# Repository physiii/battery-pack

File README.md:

# battery-pack
60v battery pack using 16 (18650) batteries with voltage level LED.

##Schematic

##Layout

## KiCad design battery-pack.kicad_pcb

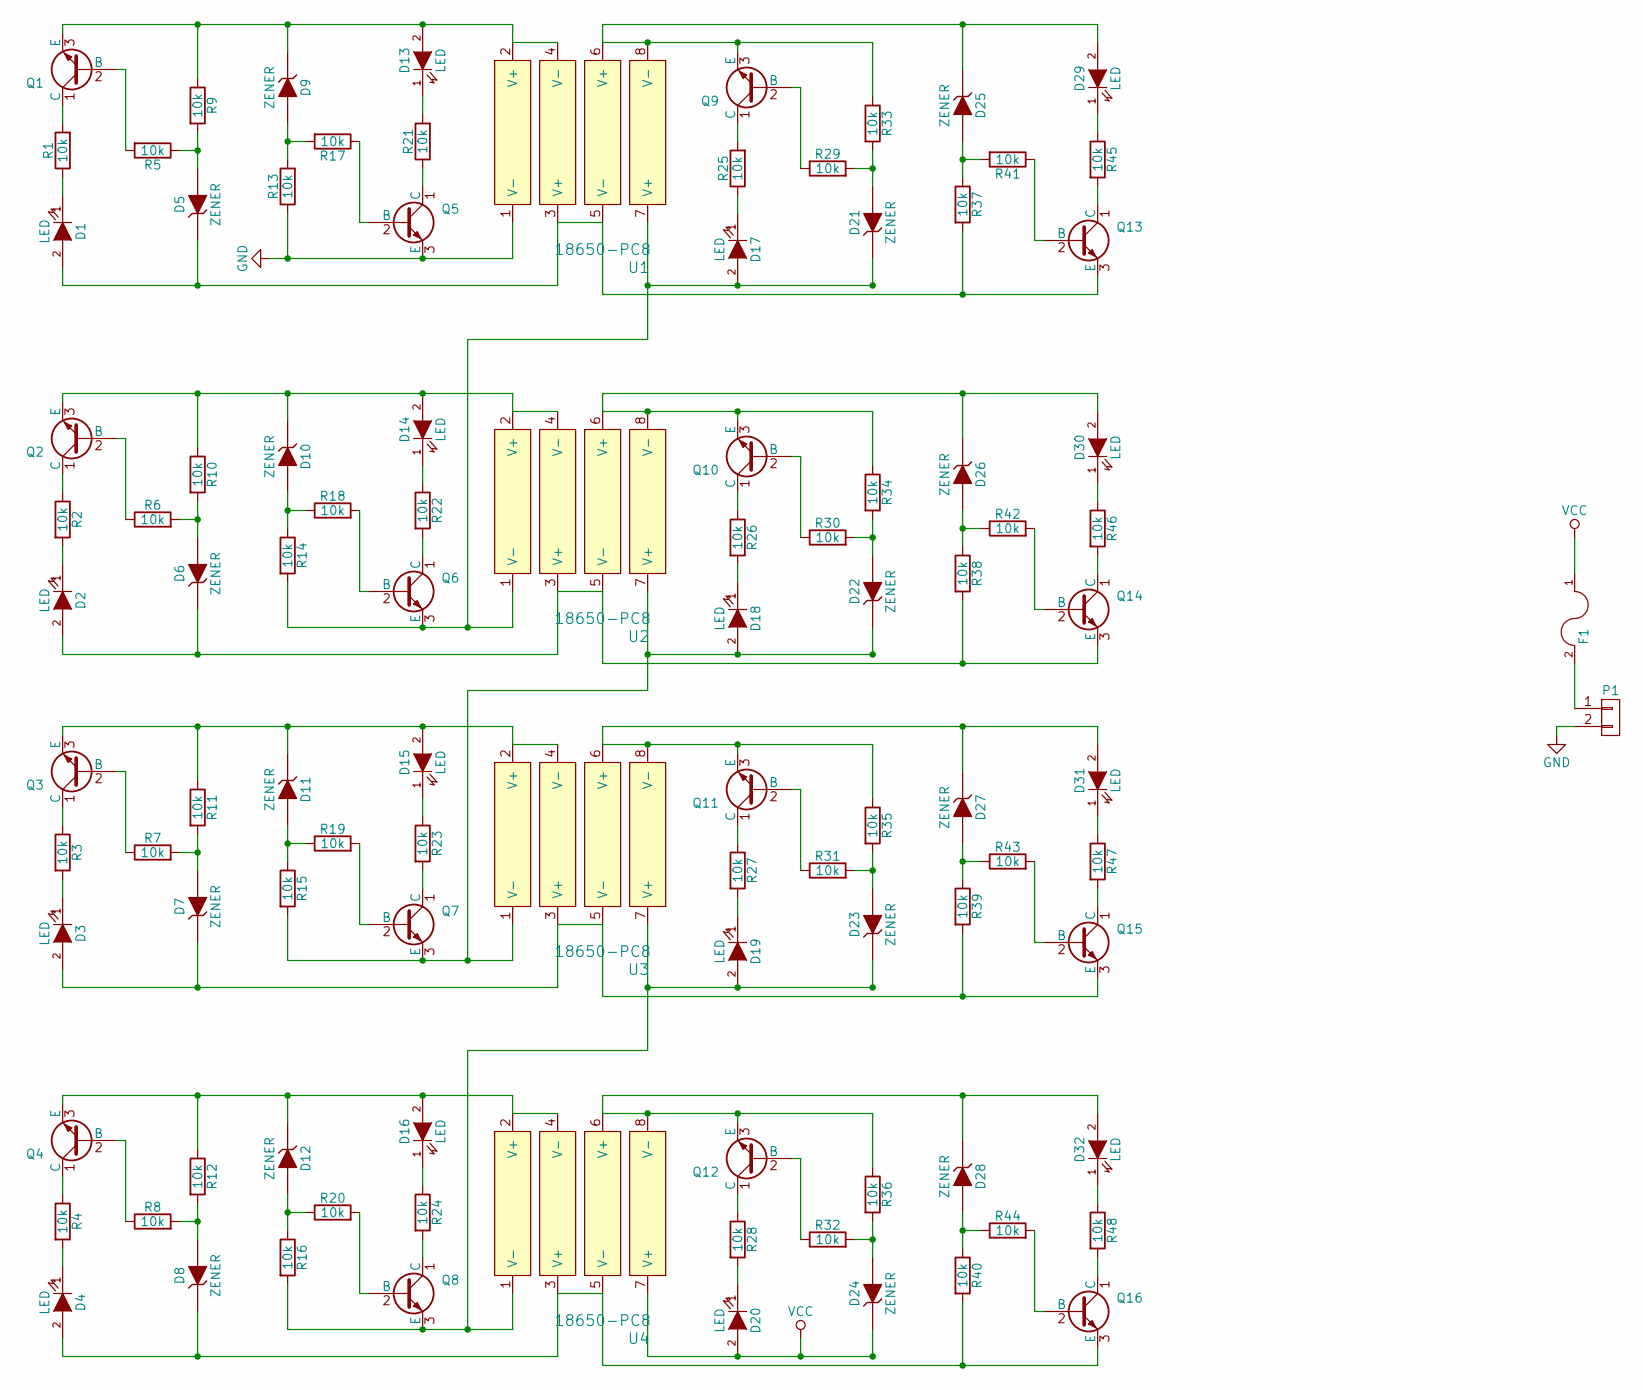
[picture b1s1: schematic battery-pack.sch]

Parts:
D1, D2, D3, D4, D13, D14, D15, D16, D17, D18, D19, D20, D29, D30, D31, D32: LED; LED_0805; Part Number LS Q976-NR-1
D5, D6, D7, D8, D9, D10, D11, D12, D21, D22, D23, D24, D25, D26, D27, D28: ZENER; SOT-23; Part Number MMBZ5229BLT1G
F1: 01000057Z; ATC_FUSE; Part Number 01000057Z
P1: CONN_01X02; TerminalBlock-ESPM02200; Part Number ESPM02200
Q1, Q2, Q3, Q4, Q5, Q6, Q7, Q8, Q9, Q10, Q11, Q12, Q13, Q14, Q15, Q16: MMBT3904LT1G; SOT-23; Part Number MMBT3904LT1G
R1, R2, R3, R4, R5, R6, R7, R8, R9, R10, R11, R12, R13, R14, R15, R16, R17, R18, R19, R20, R21, R22, R23, R24, R25, R26, R27, R28, R29, R30, R31, R32, R33, R34, R35, R36, R37, R38, R39, R40, R41, R42, R43, R44, R45, R46, R47, R48: 10k; R_0603; Part Number ERJ-3GEYJ103V
U1, U2, U3, U4: 18650-PC8; BK-18650-PC8; Part Number BK-18650-PC8

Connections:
GND: P1.2, Q5.3 (E), R13.1, U1.1 (V-)
unnamed: D1.1 (K), R1.1
unnamed: D1.2 (A), D5.1 (K), Q13.3 (E), R37.2, U1.3 (V+), U1.5 (V-)
unnamed: D2.1 (K), R2.2
unnamed: D2.2 (A), D6.1 (K), Q14.3 (E), R38.2, U2.3 (V+), U2.5 (V-)
unnamed: D3.1 (K), R3.2
unnamed: D3.2 (A), D7.1 (K), Q15.3 (E), R39.2, U3.3 (V+), U3.5 (V-)
unnamed: D4.1 (K), R4.2
unnamed: D4.2 (A), D8.1 (K), Q16.3 (E), R40.2, U4.3 (V+), U4.5 (V-)
unnamed: D5.2 (A), R5.1, R9.2
unnamed: D6.2 (A), R6.2, R10.2
unnamed: D7.2 (A), R7.2, R11.2
unnamed: D8.2 (A), R8.2, R12.2
unnamed: D9.2 (A), R13.2, R17.2
unnamed: D10.1 (K), D14.2 (A), Q2.3 (E), R10.1, U2.2 (V+), U2.4 (V-)
unnamed: D10.2 (A), R14.1, R18.1
unnamed: D11.1 (K), D15.2 (A), Q3.3 (E), R11.1, U3.2 (V+), U3.4 (V-)
unnamed: D11.2 (A), R15.1, R19.1
unnamed: D12.1 (K), D16.2 (A), Q4.3 (E), R12.1, U4.2 (V+), U4.4 (V-)
unnamed: D12.2 (A), R16.1, R20.1
unnamed: D13.1 (K), R21.2
unnamed: D9.1 (K), D13.2 (A), Q1.3 (E), R9.1, U1.2 (V+), U1.4 (V-)
unnamed: D14.1 (K), R22.1
unnamed: D15.1 (K), R23.1
unnamed: D16.1 (K), R24.1
unnamed: D17.1 (K), R25.1
unnamed: D17.2 (A), D21.1 (K), Q6.3 (E), R14.2, U1.7 (V+), U2.1 (V-)
unnamed: D18.1 (K), R26.2
unnamed: D18.2 (A), D22.1 (K), Q7.3 (E), R15.2, U2.7 (V+), U3.1 (V-)
unnamed: D19.1 (K), R27.2
unnamed: D19.2 (A), D23.1 (K), Q8.3 (E), R16.2, U3.7 (V+), U4.1 (V-)
unnamed: D20.1 (K), R28.2
unnamed: D21.2 (A), R29.2, R33.2
unnamed: D22.2 (A), R30.2, R34.2
unnamed: D23.2 (A), R31.2, R35.2
unnamed: D24.2 (A), R32.2, R36.2
unnamed: D25.1 (K), D29.2 (A), Q9.3 (E), R33.1, U1.6 (V+), U1.8 (V-)
unnamed: D25.2 (A), R37.1, R41.2
unnamed: D26.1 (K), D30.2 (A), Q10.3 (E), R34.1, U2.6 (V+), U2.8 (V-)
unnamed: D26.2 (A), R38.1, R42.1
unnamed: D27.1 (K), D31.2 (A), Q11.3 (E), R35.1, U3.6 (V+), U3.8 (V-)
unnamed: D27.2 (A), R39.1, R43.1
unnamed: D28.1 (K), D32.2 (A), Q12.3 (E), R36.1, U4.6 (V+), U4.8 (V-)
unnamed: D28.2 (A), R40.1, R44.1
unnamed: D29.1 (K), R45.1
unnamed: D30.1 (K), R46.1
unnamed: D31.1 (K), R47.1
unnamed: D32.1 (K), R48.1
unnamed: F1.2, P1.1
unnamed: Q1.1 (C), R1.2
unnamed: Q1.2 (B), R5.2
unnamed: Q2.1 (C), R2.1
unnamed: Q2.2 (B), R6.1
unnamed: Q3.1 (C), R3.1
unnamed: Q3.2 (B), R7.1
unnamed: Q4.1 (C), R4.1
unnamed: Q4.2 (B), R8.1
unnamed: Q5.1 (C), R21.1
unnamed: Q5.2 (B), R17.1
unnamed: Q6.1 (C), R22.2
unnamed: Q6.2 (B), R18.2
unnamed: Q7.1 (C), R23.2
unnamed: Q7.2 (B), R19.2
unnamed: Q8.1 (C), R24.2
unnamed: Q8.2 (B), R20.2
unnamed: Q9.1 (C), R25.2
unnamed: Q9.2 (B), R29.1
unnamed: Q10.1 (C), R26.1
unnamed: Q10.2 (B), R30.1
unnamed: Q11.1 (C), R27.1
unnamed: Q11.2 (B), R31.1
unnamed: Q12.1 (C), R28.1
unnamed: Q12.2 (B), R32.1
unnamed: Q13.1 (C), R45.2
unnamed: Q13.2 (B), R41.1
unnamed: Q14.1 (C), R46.2
unnamed: Q14.2 (B), R42.2
unnamed: Q15.1 (C), R47.2
unnamed: Q15.2 (B), R43.2
unnamed: Q16.1 (C), R48.2
unnamed: Q16.2 (B), R44.2
VCC: D20.2 (A), D24.1 (K), F1.1, U4.7 (V+)

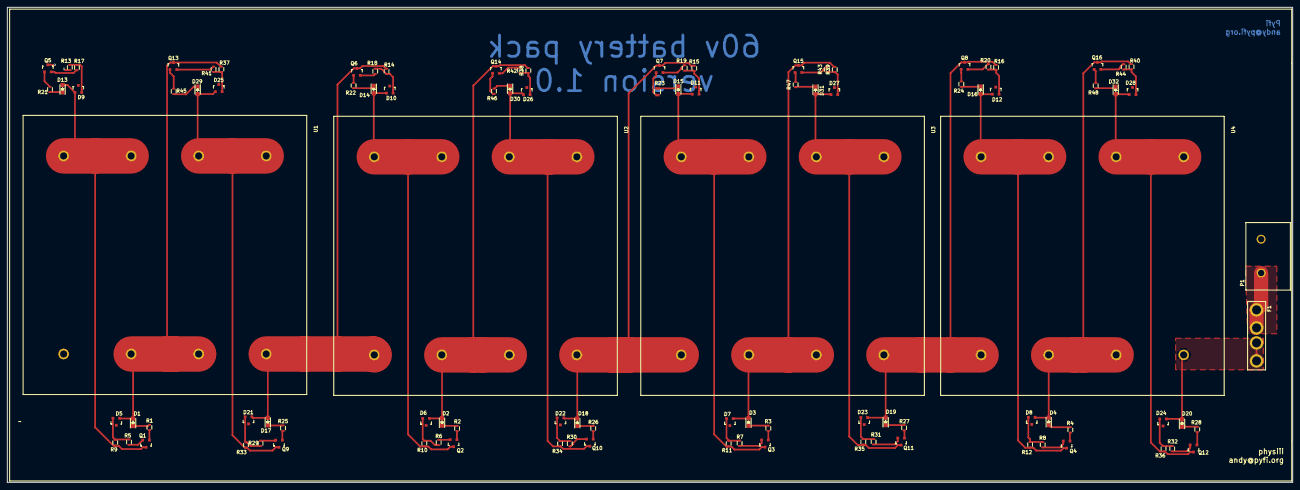
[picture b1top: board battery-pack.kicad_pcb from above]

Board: 2 copper layers, 362.6 x 134.0 mm, 102 parts (0 on the bottom side), 82 nets.

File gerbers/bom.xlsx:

Reference | Value | Footprint | Datasheet | Part Number
F1 | 01000057Z | battery-pack:ATC_FUSE | http://www.mouser.com/ds/2/240/Littelfuse_fuse-clips-186442.pdf | 01000057Z
P1 | CONN_01X02 | battery-pack:TerminalBlock-ESPM02200 | http://www.mouser.com/ds/2/18/200912210387880-199.pdf | ESPM02200
U3 | 18650-PC8 | battery-pack:BK-18650-PC8 |  | BK-18650-PC8
D11 | ZENER | TO_SOT_Packages_SMD:SOT-23 |  | MMBZ5229BLT1G
D15 | LED | LEDs:LED_0805 |  | LS Q976-NR-1
D7 | ZENER | TO_SOT_Packages_SMD:SOT-23 |  | MMBZ5229BLT1G
D3 | LED | LEDs:LED_0805 |  | LS Q976-NR-1
D23 | ZENER | TO_SOT_Packages_SMD:SOT-23 |  | MMBZ5229BLT1G
D19 | LED | LEDs:LED_0805 |  | LS Q976-NR-1
D27 | ZENER | TO_SOT_Packages_SMD:SOT-23 |  | MMBZ5229BLT1G
D31 | LED | LEDs:LED_0805 |  | LS Q976-NR-1
U4 | 18650-PC8 | battery-pack:BK-18650-PC8 |  | BK-18650-PC8
D12 | ZENER | TO_SOT_Packages_SMD:SOT-23 |  | MMBZ5229BLT1G
D16 | LED | LEDs:LED_0805 |  | LS Q976-NR-1
D8 | ZENER | TO_SOT_Packages_SMD:SOT-23 |  | MMBZ5229BLT1G
D4 | LED | LEDs:LED_0805 |  | LS Q976-NR-1
D24 | ZENER | TO_SOT_Packages_SMD:SOT-23 |  | MMBZ5229BLT1G
D20 | LED | LEDs:LED_0805 |  | LS Q976-NR-1
D28 | ZENER | TO_SOT_Packages_SMD:SOT-23 |  | MMBZ5229BLT1G
D32 | LED | LEDs:LED_0805 |  | LS Q976-NR-1
U1 | 18650-PC8 | battery-pack:BK-18650-PC8 |  | BK-18650-PC8
D9 | ZENER | TO_SOT_Packages_SMD:SOT-23 |  | MMBZ5229BLT1G
R13 | 10k | Resistors_SMD:R_0603 |  | ERJ-3GEYJ103V
D13 | LED | LEDs:LED_0805 |  | LS Q976-NR-1
D5 | ZENER | TO_SOT_Packages_SMD:SOT-23 | http://www.mouser.com/ds/2/308/MMBZ5221BLT1-D-79158.pdf | MMBZ5229BLT1G
R9 | 10k | Resistors_SMD:R_0603 |  | ERJ-3GEYJ103V
R5 | 10k | Resistors_SMD:R_0603 |  | ERJ-3GEYJ103V
R1 | 10k | Resistors_SMD:R_0603 |  | ERJ-3GEYJ103V
D1 | LED | LEDs:LED_0805 |  | LS Q976-NR-1
D21 | ZENER | TO_SOT_Packages_SMD:SOT-23 |  | MMBZ5229BLT1G
D17 | LED | LEDs:LED_0805 |  | LS Q976-NR-1
D25 | ZENER | TO_SOT_Packages_SMD:SOT-23 |  | MMBZ5229BLT1G
D29 | LED | LEDs:LED_0805 |  | LS Q976-NR-1
U2 | 18650-PC8 | battery-pack:BK-18650-PC8 |  | BK-18650-PC8
D10 | ZENER | TO_SOT_Packages_SMD:SOT-23 |  | MMBZ5229BLT1G
D14 | LED | LEDs:LED_0805 |  | LS Q976-NR-1
D6 | ZENER | TO_SOT_Packages_SMD:SOT-23 |  | MMBZ5229BLT1G
D2 | LED | LEDs:LED_0805 |  | LS Q976-NR-1
D22 | ZENER | TO_SOT_Packages_SMD:SOT-23 |  | MMBZ5229BLT1G
D18 | LED | LEDs:LED_0805 |  | LS Q976-NR-1
D26 | ZENER | TO_SOT_Packages_SMD:SOT-23 |  | MMBZ5229BLT1G
Q14 | MMBT3904LT1G | TO_SOT_Packages_SMD:SOT-23 | http://www.mouser.com/ds/2/308/MMBT3904LT1-D-113169.pdf | MMBT3904LT1G
D30 | LED | LEDs:LED_0805 |  | LS Q976-NR-1
Q13 | MMBT3904LT1G | TO_SOT_Packages_SMD:SOT-23 | http://www.mouser.com/ds/2/308/MMBT3904LT1-D-113169.pdf | MMBT3904LT1G
Q15 | MMBT3904LT1G | TO_SOT_Packages_SMD:SOT-23 | http://www.mouser.com/ds/2/308/MMBT3904LT1-D-113169.pdf | MMBT3904LT1G
Q16 | MMBT3904LT1G | TO_SOT_Packages_SMD:SOT-23 | http://www.mouser.com/ds/2/308/MMBT3904LT1-D-113169.pdf | MMBT3904LT1G
Q5 | MMBT3904LT1G | TO_SOT_Packages_SMD:SOT-23 | http://www.mouser.com/ds/2/308/MMBT3904LT1-D-113169.pdf | MMBT3904LT1G
Q6 | MMBT3904LT1G | TO_SOT_Packages_SMD:SOT-23 | http://www.mouser.com/ds/2/308/MMBT3904LT1-D-113169.pdf | MMBT3904LT1G
Q7 | MMBT3904LT1G | TO_SOT_Packages_SMD:SOT-23 | http://www.mouser.com/ds/2/308/MMBT3904LT1-D-113169.pdf | MMBT3904LT1G
Q8 | MMBT3904LT1G | TO_SOT_Packages_SMD:SOT-23 | http://www.mouser.com/ds/2/308/MMBT3904LT1-D-113169.pdf | MMBT3904LT1G
Q4 | MMBT3904LT1G | TO_SOT_Packages_SMD:SOT-23 | http://www.mouser.com/ds/2/308/MMBT3904LT1-D-113169.pdf | MMBT3904LT1G
Q3 | MMBT3904LT1G | TO_SOT_Packages_SMD:SOT-23 | http://www.mouser.com/ds/2/308/MMBT3904LT1-D-113169.pdf | MMBT3904LT1G
Q2 | MMBT3904LT1G | TO_SOT_Packages_SMD:SOT-23 | http://www.mouser.com/ds/2/308/MMBT3904LT1-D-113169.pdf | MMBT3904LT1G
Q1 | MMBT3904LT1G | TO_SOT_Packages_SMD:SOT-23 | http://www.mouser.com/ds/2/308/MMBT3904LT1-D-113169.pdf | MMBT3904LT1G
Q9 | MMBT3904LT1G | TO_SOT_Packages_SMD:SOT-23 | http://www.mouser.com/ds/2/308/MMBT3904LT1-D-113169.pdf | MMBT3904LT1G
Q10 | MMBT3904LT1G | TO_SOT_Packages_SMD:SOT-23 | http://www.mouser.com/ds/2/308/MMBT3904LT1-D-113169.pdf | MMBT3904LT1G
Q11 | MMBT3904LT1G | TO_SOT_Packages_SMD:SOT-23 | http://www.mouser.com/ds/2/308/MMBT3904LT1-D-113169.pdf | MMBT3904LT1G
Q12 | MMBT3904LT1G | TO_SOT_Packages_SMD:SOT-23 | http://www.mouser.com/ds/2/308/MMBT3904LT1-D-113169.pdf | MMBT3904LT1G
R17 | 10k | Resistors_SMD:R_0603 |  | ERJ-3GEYJ103V
R21 | 10k | Resistors_SMD:R_0603 |  | ERJ-3GEYJ103V
R25 | 10k | Resistors_SMD:R_0603 |  | ERJ-3GEYJ103V
R29 | 10k | Resistors_SMD:R_0603 |  | ERJ-3GEYJ103V
R33 | 10k | Resistors_SMD:R_0603 |  | ERJ-3GEYJ103V
R37 | 10k | Resistors_SMD:R_0603 |  | ERJ-3GEYJ103V
R45 | 10k | Resistors_SMD:R_0603 |  | ERJ-3GEYJ103V
R41 | 10k | Resistors_SMD:R_0603 |  | ERJ-3GEYJ103V
R46 | 10k | Resistors_SMD:R_0603 |  | ERJ-3GEYJ103V
R47 | 10k | Resistors_SMD:R_0603 |  | ERJ-3GEYJ103V
R48 | 10k | Resistors_SMD:R_0603 |  | ERJ-3GEYJ103V
R40 | 10k | Resistors_SMD:R_0603 |  | ERJ-3GEYJ103V
R39 | 10k | Resistors_SMD:R_0603 |  | ERJ-3GEYJ103V
R38 | 10k | Resistors_SMD:R_0603 |  | ERJ-3GEYJ103V
R34 | 10k | Resistors_SMD:R_0603 |  | ERJ-3GEYJ103V
R26 | 10k | Resistors_SMD:R_0603 |  | ERJ-3GEYJ103V
R27 | 10k | Resistors_SMD:R_0603 |  | ERJ-3GEYJ103V
R35 | 10k | Resistors_SMD:R_0603 |  | ERJ-3GEYJ103V
R36 | 10k | Resistors_SMD:R_0603 |  | ERJ-3GEYJ103V
R28 | 10k | Resistors_SMD:R_0603 |  | ERJ-3GEYJ103V
R24 | 10k | Resistors_SMD:R_0603 |  | ERJ-3GEYJ103V
R16 | 10k | Resistors_SMD:R_0603 |  | ERJ-3GEYJ103V
R4 | 10k | Resistors_SMD:R_0603 |  | ERJ-3GEYJ103V
R12 | 10k | Resistors_SMD:R_0603 |  | ERJ-3GEYJ103V
R11 | 10k | Resistors_SMD:R_0603 |  | ERJ-3GEYJ103V
R3 | 10k | Resistors_SMD:R_0603 |  | ERJ-3GEYJ103V
R15 | 10k | Resistors_SMD:R_0603 |  | ERJ-3GEYJ103V
R23 | 10k | Resistors_SMD:R_0603 |  | ERJ-3GEYJ103V
R2 | 10k | Resistors_SMD:R_0603 |  | ERJ-3GEYJ103V
R10 | 10k | Resistors_SMD:R_0603 |  | ERJ-3GEYJ103V
R14 | 10k | Resistors_SMD:R_0603 |  | ERJ-3GEYJ103V
R22 | 10k | Resistors_SMD:R_0603 |  | ERJ-3GEYJ103V
R18 | 10k | Resistors_SMD:R_0603 |  | ERJ-3GEYJ103V
R6 | 10k | Resistors_SMD:R_0603 |  | ERJ-3GEYJ103V
R7 | 10k | Resistors_SMD:R_0603 |  | ERJ-3GEYJ103V
R19 | 10k | Resistors_SMD:R_0603 |  | ERJ-3GEYJ103V
R30 | 10k | Resistors_SMD:R_0603 |  | ERJ-3GEYJ103V
R42 | 10k | Resistors_SMD:R_0603 |  | ERJ-3GEYJ103V
R43 | 10k | Resistors_SMD:R_0603 |  | ERJ-3GEYJ103V
R31 | 10k | Resistors_SMD:R_0603 |  | ERJ-3GEYJ103V
R32 | 10k | Resistors_SMD:R_0603 |  | ERJ-3GEYJ103V
R44 | 10k | Resistors_SMD:R_0603 |  | ERJ-3GEYJ103V
R8 | 10k | Resistors_SMD:R_0603 |  | ERJ-3GEYJ103V
R20 | 10k | Resistors_SMD:R_0603 |  | ERJ-3GEYJ103V

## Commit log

2015-12-27 added GND fill
2015-12-29 updated schematic
